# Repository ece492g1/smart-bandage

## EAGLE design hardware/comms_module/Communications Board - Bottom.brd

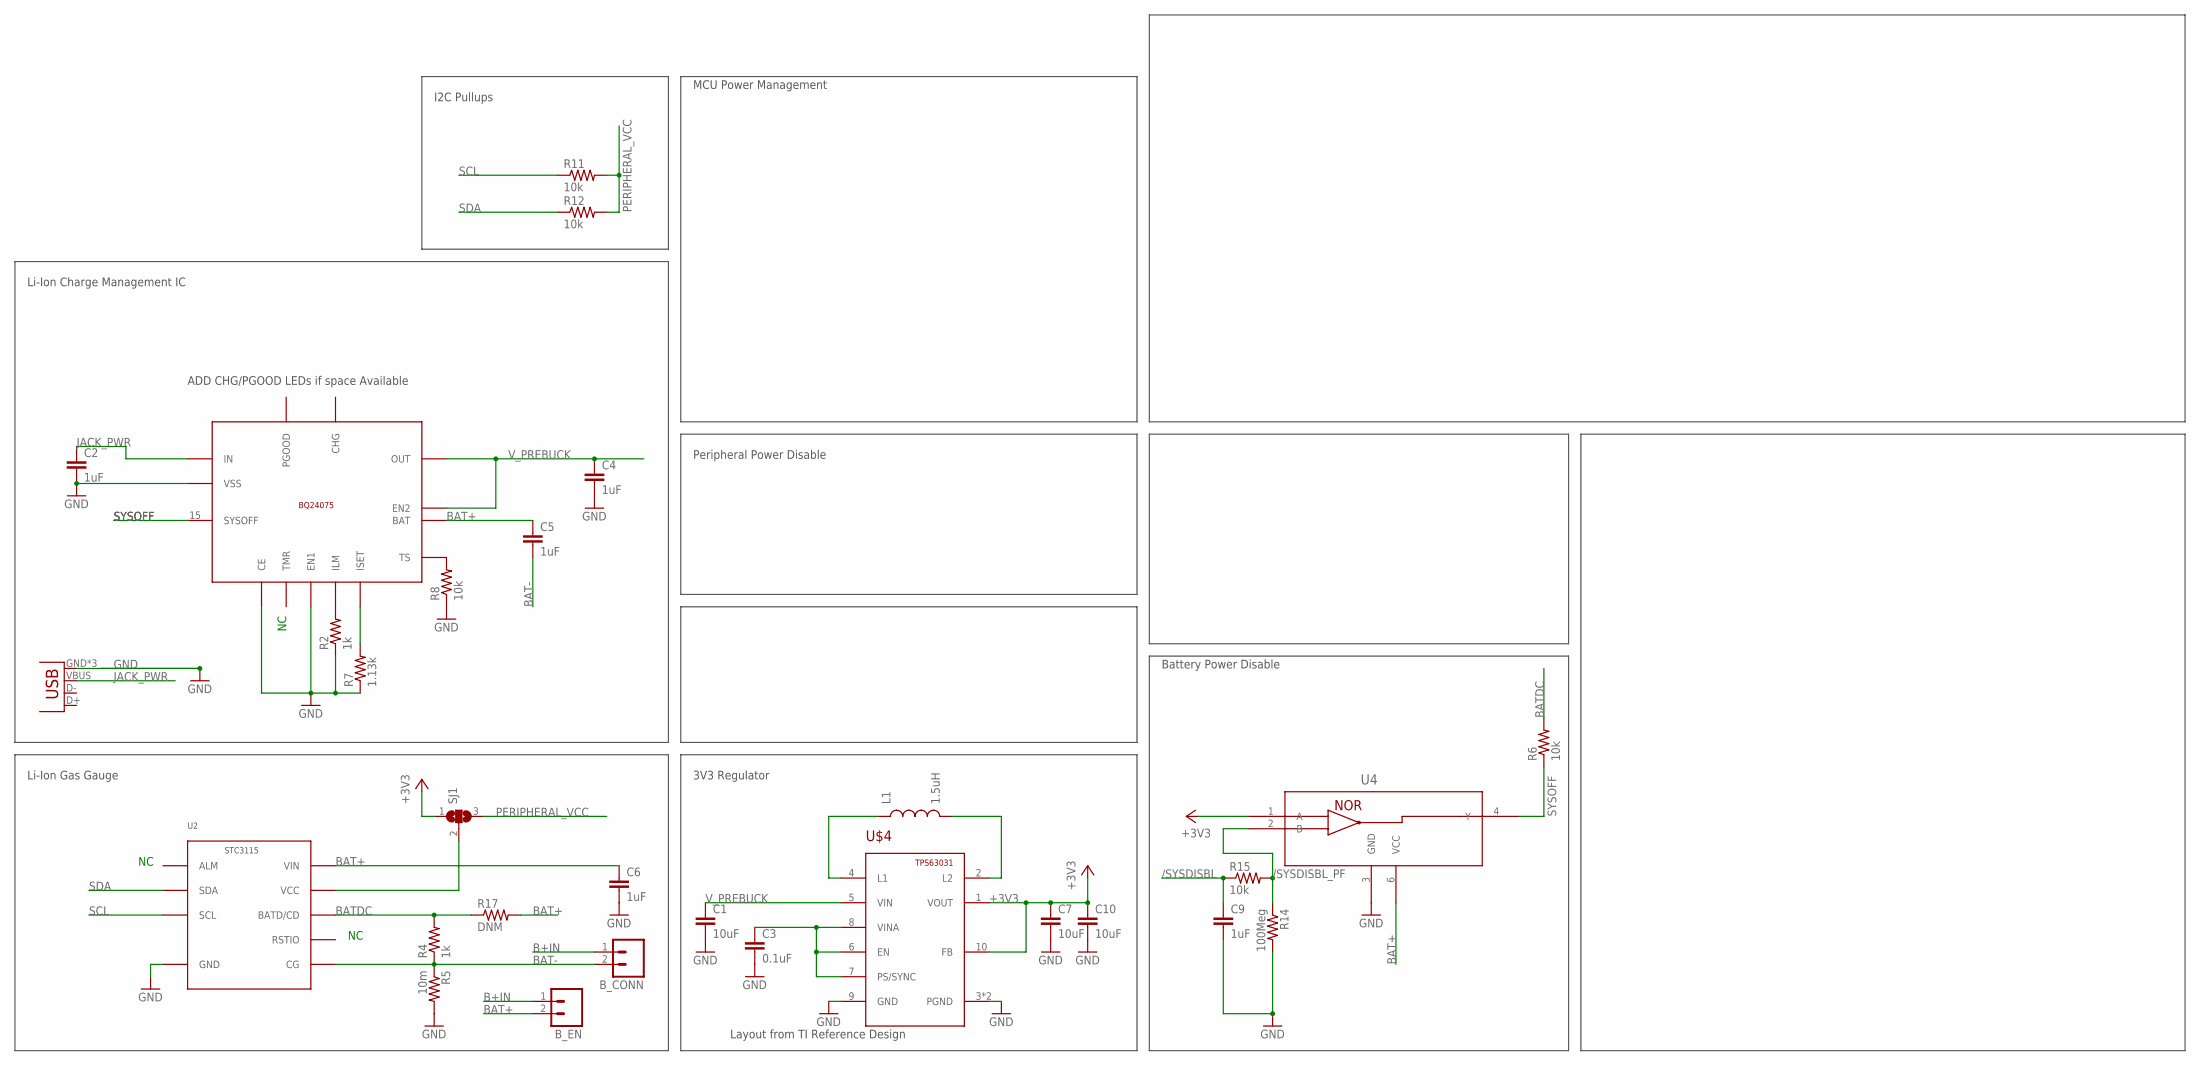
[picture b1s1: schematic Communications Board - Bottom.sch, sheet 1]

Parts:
B_CONN: M02PTH; 1X02
B_EN: M02PTH; 1X02
C1, C7: 10uF; 0402-CAP
C2, C4, C5, C6, C9: 1uF; 0603-CAP
C3: 0.1uF; 0402-CAP
C10: 10uF; 0603-CAP
L1: 1.5uH; IND1212
R2, R4: 1k; 0603-RES
R5: 10m; 0603-RES
R6, R8, R11, R12, R15: 10k; 0603-RES
R7: 1.13k; 0603-RES
R14: 100Meg; 0603-RES
R17: DNM; 0603-RES
SJ1: SJ2W; SJ_2
U2: STC3115; DFN10-2X3
U4: SN74AUP1G02_DSF_6; DSF6
U$2: BQ24075; QFN16-3X3MM
U$4: TPS63031; SON-10
X2: USB-MICROB

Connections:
+3V3: C7.1, C10.1, SJ1.1, U4.1 (A), U$4.1 (VOUT), U$4.10 (FB); also elsewhere on the board
/SYSDISBL: C9.1, R15.1; also elsewhere on the board
/SYSDISBL_PF: R14.1, R15.2, U4.2 (B)
B+IN: B_CONN.1, B_EN.1
BAT+: B_EN.2, C5.1, C6.1, R17.2, U2.P10 (VIN), U4.6 (VCC), U$2.2 (BAT), U$2.3 (BAT)
BAT-: B_CONN.2, C5.2, R4.1, R5.1, U2.P6 (CG)
BATDC: R4.2, R6.2, R17.1, U2.P8 (BATD/CD)
GND: C1.2, C2.2, C3.2, C4.2, C6.2, C7.2, C9.2, C10.2, R2.1, R5.2, R7.1, R8.1, R14.2, U2.P5 (GND), U4.3 (GND), U$2.4 (CE), U$2.6 (EN1), U$2.8 (VSS), U$2.EXT (VSS), U$4.3 (PGND), U$4.9 (GND), U$4.PAD (PGND), X2.GND, X2.MT1 (GND), X2.MT2 (GND); also elsewhere on the board
JACK_PWR: C2.1, U$2.13 (IN), X2.VBUS
unnamed: L1.P$1 (1), U$4.4 (L1)
unnamed: L1.P$2 (2), U$4.2 (L2)
unnamed: C3.1, U$4.6 (EN), U$4.7 (PS/SYNC), U$4.8 (VINA)
unnamed: R8.2, U$2.1 (TS)
unnamed: R2.2, U$2.12 (ILM)
unnamed: R7.2, U$2.16 (ISET)
unnamed: SJ1.2, U2.P9 (VCC)
PERIPHERAL_VCC: R11.2, R12.2, SJ1.3; also elsewhere on the board
SCL: R11.1, U2.P3 (SCL); also elsewhere on the board
SDA: R12.1, U2.P2 (SDA); also elsewhere on the board
SYSOFF: R6.1, U4.4 (Y), U$2.15 (SYSOFF)
V_PREBUCK: C1.1, C4.1, U$2.5 (EN2), U$2.10 (OUT), U$2.11 (OUT), U$4.5 (VIN); also elsewhere on the board

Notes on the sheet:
Li-Ion Gas Gauge
Li-Ion Charge Management IC
I2C Pullups
Layout from TI Reference Design
3V3 Regulator
Peripheral Power Disable
Battery Power Disable
ADD CHG/PGOOD LEDs if space Available
MCU Power Management

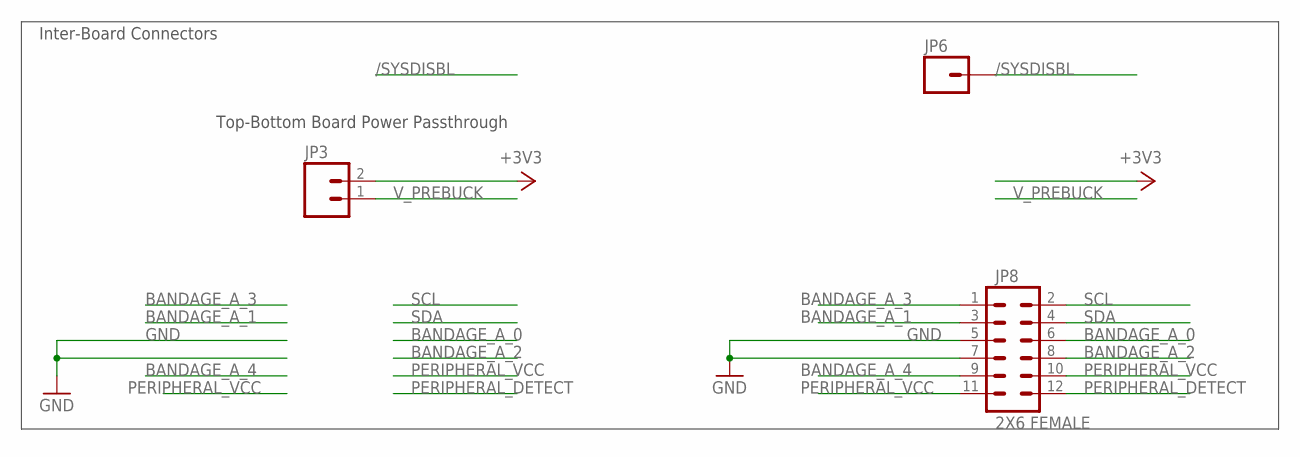
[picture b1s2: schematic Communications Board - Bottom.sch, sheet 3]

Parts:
JP3: M021X02_NO_SILK; 1X02_NO_SILK
JP6: M01PTH; 1X01
JP8: 2X6 FEMALE; 2X6

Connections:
+3V3: JP3.2; also elsewhere on the board
/SYSDISBL: JP6.1; also elsewhere on the board
BANDAGE_A_0: JP8.6
BANDAGE_A_1: JP8.3
BANDAGE_A_2: JP8.8
BANDAGE_A_3: JP8.1
BANDAGE_A_4: JP8.9
GND: JP8.5, JP8.7; also elsewhere on the board
PERIPHERAL_DETECT: JP8.12
PERIPHERAL_VCC: JP8.10, JP8.11; also elsewhere on the board
SCL: JP8.2; also elsewhere on the board
SDA: JP8.4; also elsewhere on the board
V_PREBUCK: JP3.1; also elsewhere on the board

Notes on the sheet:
Top-Bottom Board Power Passthrough
Inter-Board Connectors

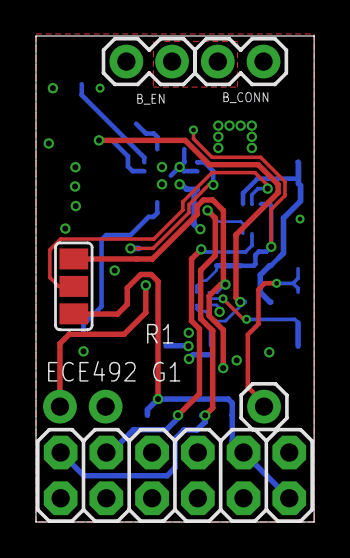
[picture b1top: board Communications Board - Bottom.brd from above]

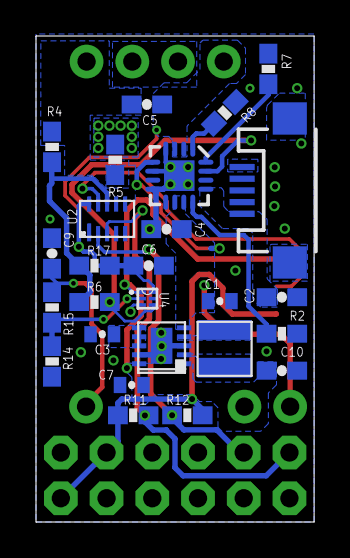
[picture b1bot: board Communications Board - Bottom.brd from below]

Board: 2 copper layers, 15.4 x 27.0 mm, 32 parts (26 on the bottom side), 21 nets.

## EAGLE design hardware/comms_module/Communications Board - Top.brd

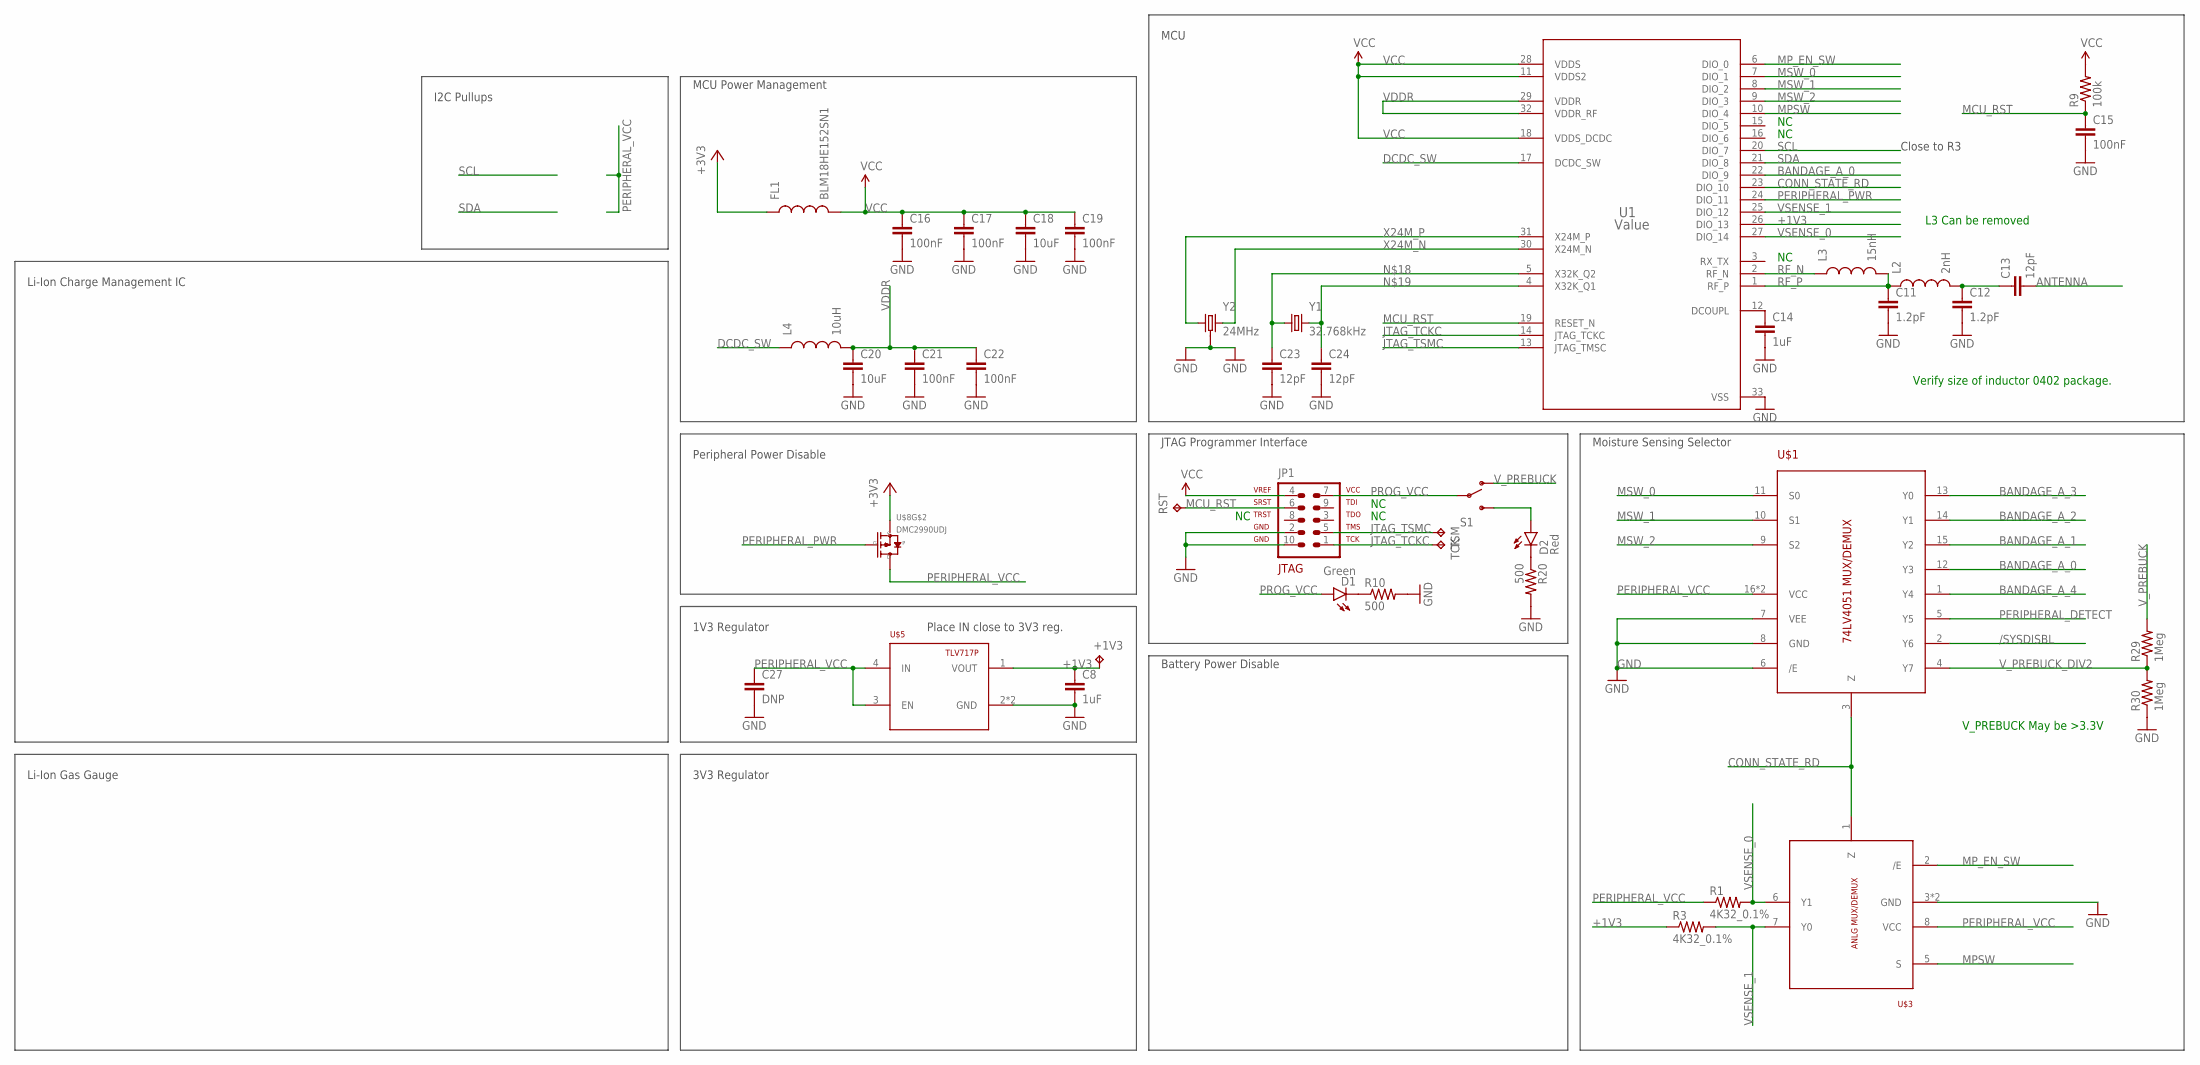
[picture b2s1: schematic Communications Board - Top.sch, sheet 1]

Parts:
+1V3: TPTP10R; TP10R
C8, C14: 1uF; 0402-CAP
C11, C12: 1.2pF; 0402-CAP
C13, C23, C24: 12pF; 0402-CAP
C15, C16, C17, C19, C21, C22: 100nF; 0402-CAP
C18, C20: 10uF; 0402-CAP
C27: DNP; 0402-CAP
D1: Green; LED-1206
D2: Red; LED-1206
FL1: BLM18HE152SN1; 0603
JP1: AVR-JTAG-10
L2: 2nH; C0402
L3: 15nH; C0402
L4: 10uH; 0603
R1, R3: 4K32_0.1%; 0402-RES
R9: 100k; 0603-RES
R10, R20: 500; 0603-RES
R29, R30: 1Meg; 0402-RES
RST: TPTP10R; TP10R
S1: SWITCH-SPDT; JS102011SAQN
TCK: TPTP10R; TP10R
TSM: TPTP10R; TP10R
U1: Value; RHB0032E
U$1: 74LV4051; SOT763-1
U$3: 74LVC2G53; SOT833-1
U$5: TLV717P; X2SON
U$8: DMC2990UDJ; SOT963
Y1: 32.768kHz; CRYSTAL-3.2X1.5
Y2: 24MHz; TSX-3225

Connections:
+1V3: +1V3.TP, C8.1, R3.1, U1.26 (DIO_13), U$5.1 (VOUT)
+3V3: FL1.1, U$8.4 (S); also elsewhere on the board
/SYSDISBL: U$1.2 (Y6); also elsewhere on the board
ANTENNA: C13.2
BANDAGE_A_0: U1.22 (DIO_9), U$1.12 (Y3); also elsewhere on the board
BANDAGE_A_1: U$1.15 (Y2); also elsewhere on the board
BANDAGE_A_2: U$1.14 (Y1); also elsewhere on the board
BANDAGE_A_3: U$1.13 (Y0); also elsewhere on the board
BANDAGE_A_4: U$1.1 (Y4); also elsewhere on the board
CONN_STATE_RD: U1.23 (DIO_10), U$1.3 (Z), U$3.1 (Z)
DCDC_SW: L4.1, U1.17 (DCDC_SW)
GND: C8.2, C11.2, C12.2, C14.2, C15.2, C16.2, C17.2, C18.2, C19.2, C20.2, C21.2, C22.2, C23.2, C24.2, C27.2, JP1.2, JP1.10, R10.2, R20.2, R30.1, U1.33 (VSS), U$1.6 (/E), U$1.7 (VEE), U$1.8 (GND), U$3.3 (GND), U$3.4 (GND), U$5.2 (GND), U$5.PAD (GND), Y2.2 (3), Y2.4 (3); also elsewhere on the board
JTAG_TCKC: JP1.1, TCK.TP, U1.14 (JTAG_TCKC)
JTAG_TSMC: JP1.5, TSM.TP, U1.13 (JTAG_TMSC)
MCU_RST: C15.1, JP1.6, R9.1, RST.TP, U1.19 (RESET_N)
MPSW: U1.10 (DIO_4), U$3.5 (S)
MP_EN_SW: U1.6 (DIO_0), U$3.2 (/E)
MSW_0: U1.7 (DIO_1), U$1.11 (S0)
MSW_1: U1.8 (DIO_2), U$1.10 (S1)
MSW_2: U1.9 (DIO_3), U$1.9 (S2)
unnamed: D2.A, S1.3 (S)
unnamed: D2.C, R20.1
unnamed: C23.1, U1.5 (X32K_Q2), Y1.1
unnamed: C24.1, U1.4 (X32K_Q1), Y1.2
unnamed: D1.C, R10.1
unnamed: C12.1, C13.1, L2.2
unnamed: C14.1, U1.12 (DCOUPL)
PERIPHERAL_DETECT: U$1.5 (Y5); also elsewhere on the board
PERIPHERAL_PWR: U1.24 (DIO_11), U$8.5 (G)
PERIPHERAL_VCC: C27.1, R1.1, U$1.16 (VCC), U$1.PAD (VCC), U$3.8 (VCC), U$5.3 (EN), U$5.4 (IN), U$8.3 (D); also elsewhere on the board
PROG_VCC: D1.A, JP1.7, S1.2
RF_N: L3.1, U1.2 (RF_N)
RF_P: C11.1, L2.1, L3.2, U1.1 (RF_P)
SCL: U1.20 (DIO_7); also elsewhere on the board
SDA: U1.21 (DIO_8); also elsewhere on the board
VCC: C16.1, C17.1, C18.1, C19.1, FL1.2, JP1.4, R9.2, U1.11 (VDDS2), U1.18 (VDDS_DCDC), U1.28 (VDDS); also elsewhere on the board
VDDR: C20.1, C21.1, C22.1, L4.2, U1.29 (VDDR), U1.32 (VDDR_RF)
VSENSE_0: R1.2, U1.27 (DIO_14), U$3.6 (Y1)
VSENSE_1: R3.2, U1.25 (DIO_12), U$3.7 (Y0)
V_PREBUCK: R29.2, S1.1 (O); also elsewhere on the board
V_PREBUCK_DIV2: R29.1, R30.2, U$1.4 (Y7)
X24M_N: U1.30 (X24M_N), Y2.3 (2)
X24M_P: U1.31 (X24M_P), Y2.1

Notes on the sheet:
Li-Ion Gas Gauge
Li-Ion Charge Management IC
I2C Pullups
Close to R3
3V3 Regulator
1V3 Regulator
Place IN close to 3V3 reg.
Peripheral Power Disable
Battery Power Disable
Verify size of inductor 0402 package.
L3 Can be removed
JTAG Programmer Interface
V_PREBUCK May be >3.3V
MCU Power Management
MCU
Moisture Sensing Selector

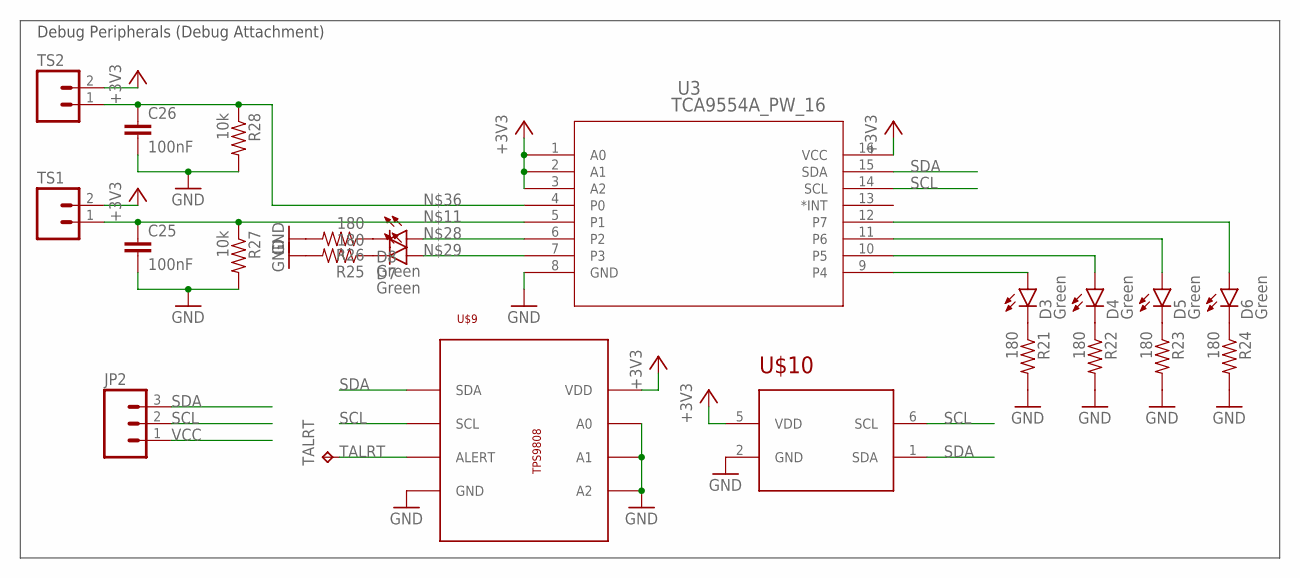
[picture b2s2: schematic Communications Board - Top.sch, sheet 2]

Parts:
C25, C26: 100nF; 0402-CAP
D3, D4, D5, D6, D7, D8: Green; LED-1206
JP2: M03PTH; 1X03
R21, R22, R23, R24, R25, R26: 180; 0603-RES
R27, R28: 10k; 0603-RES
TALRT: TPTP17R; TP17R
TS1, TS2: M02PTH; 1X02
U3: TCA9554A_PW_16; PW16
U$9: MCP9808; MSOP8
U$10: HDC1050; SON-6

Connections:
+3V3: TS1.2, TS2.2, U3.1 (A0), U3.2 (A1), U3.3 (A2), U3.16 (VCC), U$9.8 (VDD), U$10.5 (VDD); also elsewhere on the board
GND: C25.2, C26.2, R21.2, R22.2, R23.2, R24.2, R25.2, R26.2, R27.2, R28.2, U3.8 (GND), U$9.4 (GND), U$9.5 (A2), U$9.6 (A1), U$9.7 (A0), U$10.2 (GND); also elsewhere on the board
unnamed: D3.A, U3.9 (P4)
unnamed: C25.1, R27.1, TS1.1, U3.5 (P1)
unnamed: D4.A, U3.10 (P5)
unnamed: D5.A, U3.11 (P6)
unnamed: D6.A, U3.12 (P7)
unnamed: D8.A, U3.6 (P2)
unnamed: D7.A, U3.7 (P3)
unnamed: D3.C, R21.1
unnamed: D4.C, R22.1
unnamed: D5.C, R23.1
unnamed: D6.C, R24.1
unnamed: D7.C, R25.1
unnamed: D8.C, R26.1
unnamed: C26.1, R28.1, TS2.1, U3.4 (P0)
SCL: JP2.2, U3.14 (SCL), U$9.2 (SCL), U$10.6 (SCL); also elsewhere on the board
SDA: JP2.3, U3.15 (SDA), U$9.1 (SDA), U$10.1 (SDA); also elsewhere on the board
TALRT: TALRT.TP, U$9.3 (ALERT)
VCC: JP2.1; also elsewhere on the board

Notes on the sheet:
Debug Peripherals (Debug Attachment)

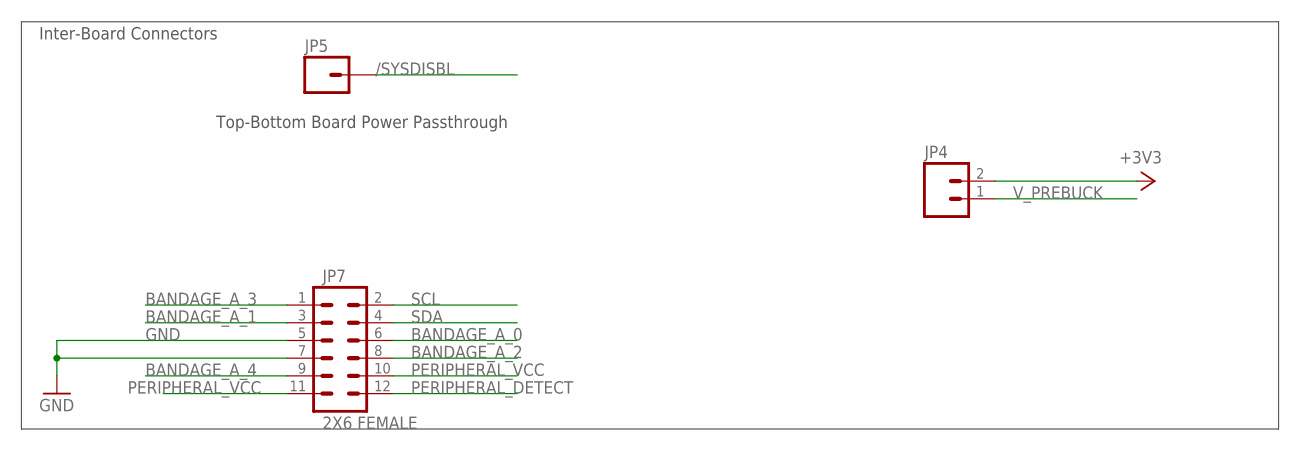
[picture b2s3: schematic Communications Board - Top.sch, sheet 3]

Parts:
JP4: M021X02_NO_SILK; 1X02_NO_SILK
JP5: M01PTH; 1X01
JP7: 2X6 FEMALE; 2X6

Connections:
+3V3: JP4.2; also elsewhere on the board
/SYSDISBL: JP5.1; also elsewhere on the board
BANDAGE_A_0: JP7.6; also elsewhere on the board
BANDAGE_A_1: JP7.3; also elsewhere on the board
BANDAGE_A_2: JP7.8; also elsewhere on the board
BANDAGE_A_3: JP7.1; also elsewhere on the board
BANDAGE_A_4: JP7.9; also elsewhere on the board
GND: JP7.5, JP7.7; also elsewhere on the board
PERIPHERAL_DETECT: JP7.12; also elsewhere on the board
PERIPHERAL_VCC: JP7.10, JP7.11; also elsewhere on the board
SCL: JP7.2; also elsewhere on the board
SDA: JP7.4; also elsewhere on the board
V_PREBUCK: JP4.1; also elsewhere on the board

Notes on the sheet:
Top-Bottom Board Power Passthrough
Inter-Board Connectors

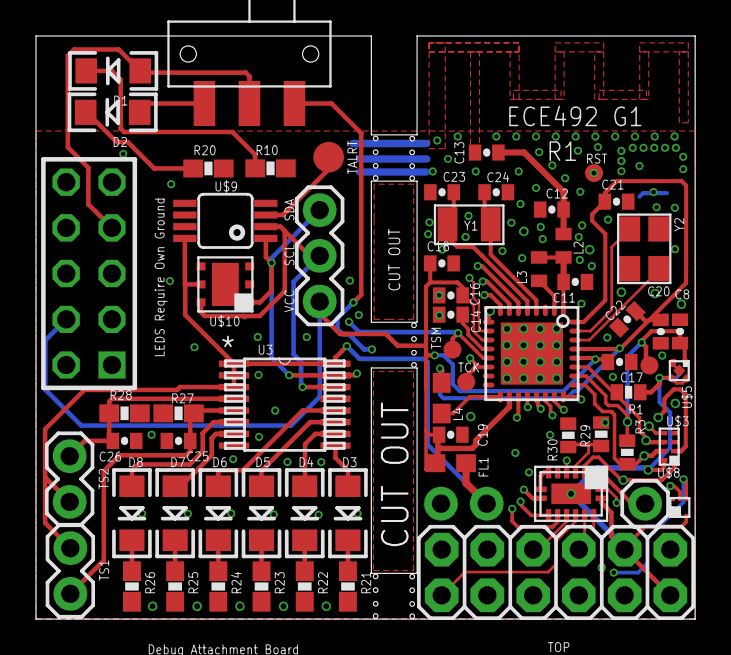
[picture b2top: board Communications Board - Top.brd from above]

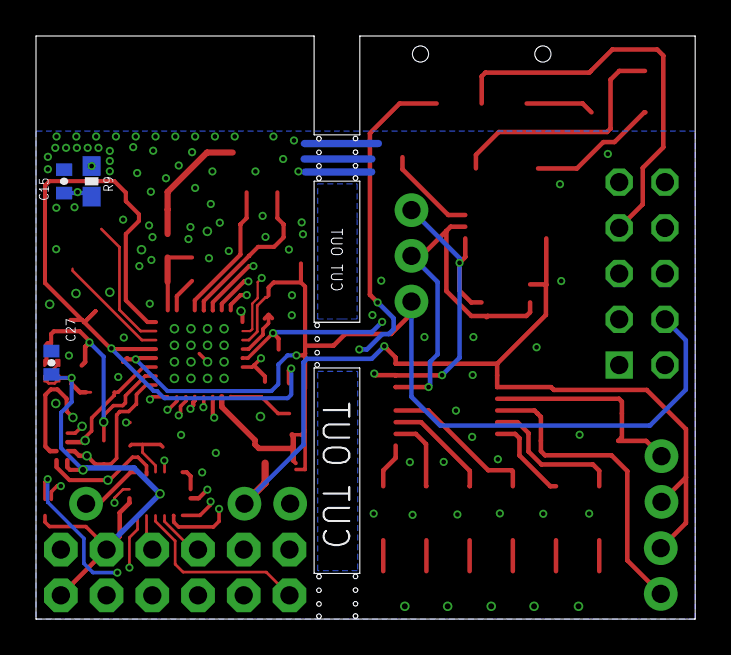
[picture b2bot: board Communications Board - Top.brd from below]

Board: 4 copper layers, 36.6 x 32.4 mm, 68 parts (3 on the bottom side), 57 nets.

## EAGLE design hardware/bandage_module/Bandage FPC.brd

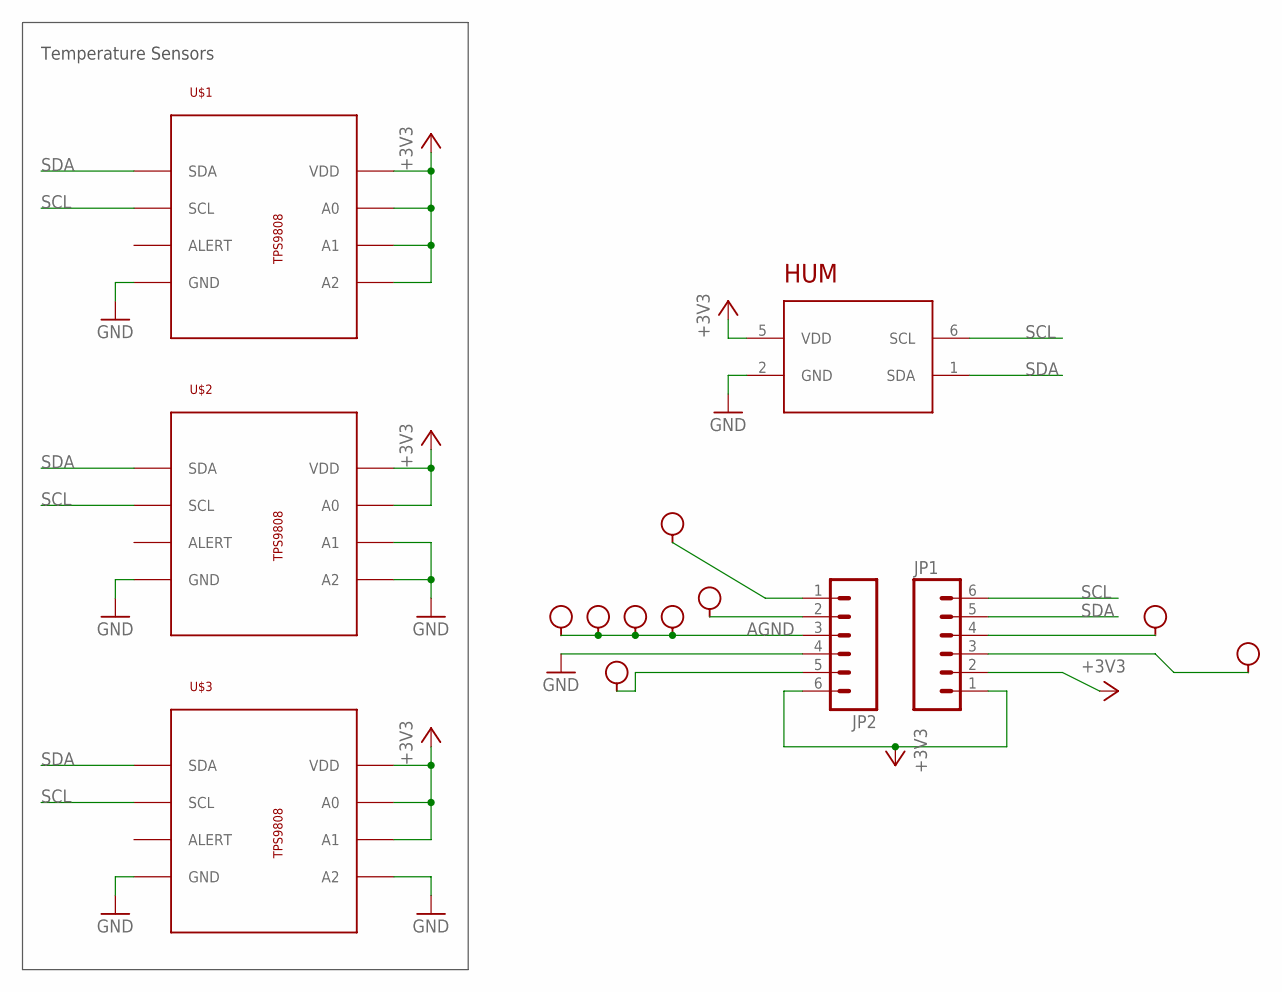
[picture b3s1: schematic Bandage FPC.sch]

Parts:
H1, H2, H3, H4, H5, H6, H7, H8, H9: SEW_HOLE-SMALL; SIMPLE_HOLE_SM
HUM: HDC1050; SON-6
JP1, JP2: M06LOCK; 1X06_LOCK
U$1, U$2, U$3: MCP9808; MSOP8

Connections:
+3V3: HUM.5 (VDD), JP1.1, JP1.2, JP2.6, U$1.5 (A2), U$1.6 (A1), U$1.7 (A0), U$1.8 (VDD), U$2.7 (A0), U$2.8 (VDD), U$3.6 (A1), U$3.7 (A0), U$3.8 (VDD)
AGND: H6.P$1, H7.P$1, H8.P$1, H9.P$1, JP2.3
GND: HUM.2 (GND), JP2.4, U$1.4 (GND), U$2.4 (GND), U$2.5 (A2), U$2.6 (A1), U$3.4 (GND), U$3.5 (A2)
unnamed: H2.P$1, JP1.3
unnamed: H1.P$1, JP2.5
unnamed: H4.P$1, JP2.2
unnamed: H3.P$1, JP1.4
unnamed: H5.P$1, JP2.1
SCL: HUM.6 (SCL), JP1.6, U$1.2 (SCL), U$2.2 (SCL), U$3.2 (SCL)
SDA: HUM.1 (SDA), JP1.5, U$1.1 (SDA), U$2.1 (SDA), U$3.1 (SDA)

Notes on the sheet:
Temperature Sensors

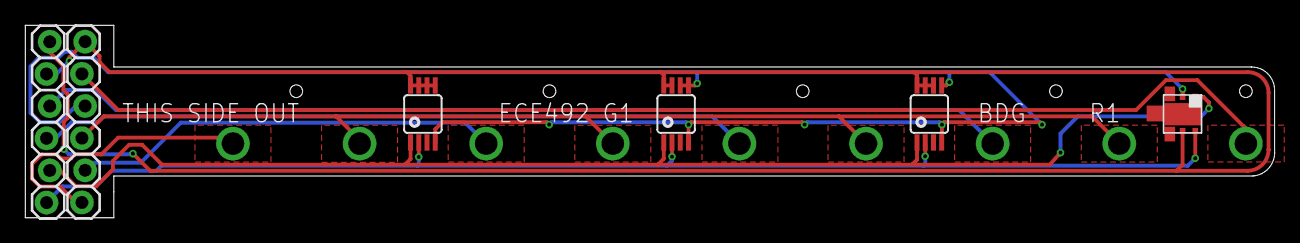
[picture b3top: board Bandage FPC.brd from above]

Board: 2 copper layers, 98.7 x 15.2 mm, 15 parts (0 on the bottom side), 10 nets.

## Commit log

2016-01-16 Initial commit of WIP board files.
2016-01-18 Add MUXes and moisture detection schematics.
2016-01-18 Add power management components.
2016-01-19 Fix STC3115 Vcc connection
2016-01-21 Add bandage module. Add HDC1050 to lib.
2016-01-23 Adding resources.md.
2016-01-27 Add remaining components and start board layout.
2016-01-27 Continued routing of the communications board.
2016-01-28 Continued routing of top and bottom.
2016-01-29 Convert to 4 layer. Nearly complete routing.
2016-01-31 App PCB Trace Antenna
2016-01-31 Nearly complete routing. Add programming interface.
2016-02-01 Continued routing of signals.
2016-02-01 Add programming attachment board.
2016-02-01 Complete programming/debug attachment board.
2016-02-02 Create muiltiple schematic sheets, and organize
2016-02-03 Update CC2650 part for batter pad sizing.
2016-02-03 Add extra cap footprint for the 1V3 regulator.
2016-02-07 Fixes from PCB review session.
2016-02-08 finite state machine and test program
2016-02-08 changed state machine location
2016-02-08 readded state machine
2016-02-08 updated finite state machine
2016-02-08 updated state machine
2016-02-09 Replace poweroff circuit with NOR gate.
2016-02-09 Finish routing of modified boards.
2016-02-09 Adding final version before split.
2016-02-09 Adding broken-out versions of top and bottom boards as ordered.
2016-02-09 Importing base TI RTOS/BLE Project.
    Based off of the `SimpleBLEPeripheral` Example Project.
2016-02-09 Adding project files to allow proper opening
2016-02-09 Add more CCS files.
2016-02-09 Update variables for system compatibility
2016-02-09 Add required library files
    Shouldn't have to do this but CCS is acting funny.
2016-02-09 Linking to included libraries.
2016-02-09 Remove non-project files where possible.
    This files are provided by various SDKs and having a copy in the project
    is confusing.
    From now on any folders with a white square icon in CCS should not be
    edited as they are not a part of the project.
2016-02-09 Fixing latent build issues and ignoring files.
2016-02-09 Adding README for project setup.
2016-02-10 Adding and Configuring I2C driver, board settings
2016-02-10 Removing executable in source.
2016-02-10 Fix I2C port numbers.
2016-02-10 Adding barebones MUX interfaces
    See #13
2016-02-10 Add definitions for a number of hardware params
    See #12
2016-02-12 Add configuration settings
2016-02-12 Add the I2C code and headers for MCP9808.
    The I2C code implements a multi-threaded I2C interface.
    The MCP9808 headers are not complete. It could likely use some convenience
    functions, and some functions for the configuration.
    See #5, #6
2016-02-12 Increase I2C frequency to 400kHz
2016-02-12 Add LED status indication to I2C temp read
    For a demonstration of PIN interfacing.
2016-02-16 Initial BLE work.
2016-02-16 Have bluetooth working with SimpleBLEPeripheral
    Integrated the SimpleBLEPeripheral code with the project code and got
    things working. Can see the temperature sensor being read, and can read
    the canned attributes from the device.
2016-02-17 Have bluetooth characteristics talking to phones
    Not sending any important data, just reading/writing. Needs verification.
    Closes #10
2016-02-17 Read temperature over bluetooth.
    See #11, #10, #6
2016-02-18 Add defines for HDC1050
    See #7
2016-02-18 Add STC3115 device header to project.
    Added a struct for the device that allows easily reading/writing the
    device.
2016-02-18 Configuration code for HDC1050, improve sensor defs
2016-02-18 Fix small peripheral manager bug
2016-02-18 Move MCP9808 implementation to .c file.
2016-02-18 Update the FSM for integration
    Reduced task stack sizes to minimum due to running out of heap memory. More
    optimizations may be neccesary.
    See #22
2016-02-19 super skeleton
2016-02-20 added skeleton for event handler
2016-02-20 Fix writing multibyte values for system time
2016-02-20 Remove commented code.
2016-02-22 basically back to square one
2016-02-22 not compiling, but pseudo outline included
2016-02-27 Add ability to run stack project individually.
2016-02-27 Add defines for running properly on the actual PCB
2016-02-27 Add peripheral management functions
    Add functions for managing external peripheral power
    Add functions for managing external MUXs and selecting desired
    inputs/outputs #13
    Configure input pins used by/for peripherals
2016-02-27 Add IOExpander management code
    Definitions and initialization
    Closes #19
2016-02-27 Add draft i2c timeout code
2016-02-27 Add IOExpander functions for status indication
2016-02-27 still just skeletons
2016-02-27 fixed compile issue, still skeleton
2016-02-28 Fix nasty bug in ICall framework, inc. heap
    Fixed a nasty bug in the ICall framework on line 1241 of ICall.c wherein
    it was trying to start a timer with timeout 0 (not allowed) and getting
    stuck in an ON error loop. This fix doesn't fix whatever was causing this,
    but afterwards it all seems to work.
    Increased the size of the heap because we were running out. Commented out
    FSM.c. We don't have enough memory for that function pointer struct
2016-02-28 Reading HDC1050 Temp and Humidity over BLE
2016-02-28 it compiles..but
2016-02-28 seg fault, line 197..fix it
2016-02-28 Opt. memory. Restructure pmanager code optimally.
    Optimized memory by reducing extra semaphores, reduce I2C stack size (it
    doesn't change much), and set the compiler to optimization level 5.
    Restructured the peripheral manager code so that it configures each device
    and starts its conversion cycle on each cycle, which is more akin to what
    we'll see with proper power management. This method also optimally
    interweaves the conversion time for all of the devices with other
2016-02-28 Adding final draft of FPC
2016-02-29 got rid of segmentation fault part add
2016-02-29 baby steps
2016-03-02 working version of callback registration system for cases where all callbacks in list will be for the same state change
2016-03-02 added in preventing of context switching for tasks while going through callbacks in linked list
2016-03-02 added callbacks dependant on state change
2016-03-03 Adding final version of the FPC board
2016-03-04 oops
2016-03-05 added UI mockup for android application
2016-03-16 Lay groundwork for flash NV storage module
    Started writing a custom flash manager as the built in osal nv stuff only
    allows for two pages (8k).
2016-03-16 Saving readings working, but not past page boundary
2016-03-16 BATT GAS BLE
2016-03-16 Add work on flash and STC3115
2016-03-16 Defined historical data bluetooth characteristics.
    Not fully hooked up yet, but readable from a bluetooth device. Had to
    reduce task stacks further to make room.
    See #15
2016-03-16 Add finalized STC3115 structures.
    Cannot yet read correct battery SOC.
    See #8
2016-03-16 Baseline working for historical data implementation
2016-03-16 Work on the notification of BLE attributes.
    This commit contains the showstopper bluetooth I believe is caused by
    talking to the bluetooth stack from the peripheral manager task as opposed
    to a thread registered through ICall
2016-03-16 Support notifications for readings.
    Seems to work properly, however android oftentimes does not receive
    notification after either connect/disconnect or reading/writing any other
    characteristic. Unclear where the bug is.
2016-03-16 Working BLE historical data transfer.
    Historical data can be transferred quickly, in bulk, using BLE
    Notification + Writeback or just BLE Indications.
    Closes #15
2016-03-16 Remove commented code and wasted stack space
2016-03-16 Minor adjustments and cleanup to FSM
2016-03-16 Missed variable rename
2016-03-20 Integrate FSM with system and work on better bluetooth connection
2016-03-20 More updates for working BLE transmit state
2016-03-20 Clear flash when all entries read
2016-03-21 Have working analog reading from bandage module.
    May be missing inputs/not reporting them
2016-03-22 Add base implementation of clock module.
    Not yet tested.
2016-03-24 Code cleaning. Flash blue LED when in transmit
2016-03-31 Fix timestamps and remove reading ref time field
    Reading reference time now reported as first 4 bytes of `Readings`.
2016-04-01 Fix power mgmt output
2016-04-01 Disable PWR MGMT
2016-04-04 Fix improper behaviour when setting timestamp the first time.
    Flash manager should have considered the time diff of the _last_ value not
    the first one.
2016-04-05 Add the extra data characteristics.
    Characteristics used for setting various operational control values.
2016-04-07 Fix moisture detection
2016-04-08 Code cleaning
2017-11-11 Add EDRC.yml
2017-11-13 Update 2
2017-12-16 Set DRU file
2017-12-16 Split out files
2017-12-17 Fix build errors
2017-12-17 fix spacing

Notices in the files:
parts and their libraries:
LilyPad-Wearables: Licensing:Creative Commons ShareAlike 4.0 International - https://creativecommons.org/licenses/by-sa/4.0
SparkFun: Licensing: CC v3.0 Share-Alike You are welcome to use this library for commercial purposes.
